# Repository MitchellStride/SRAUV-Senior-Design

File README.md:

# SRAUV-Senior-Design

## RPi Expansion PCB

## Cheap Quick Eth Breakout

## RGB Indicator Potted

## Misc. Small Breakouts & Leak Sensor

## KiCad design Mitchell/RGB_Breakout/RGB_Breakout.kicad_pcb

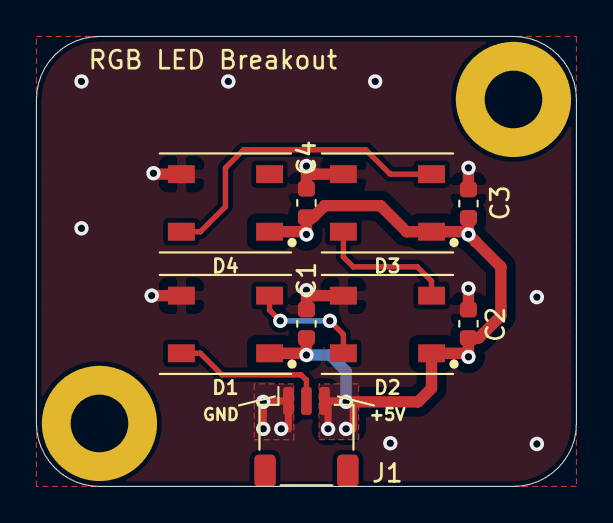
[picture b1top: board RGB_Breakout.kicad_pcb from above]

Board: 2 copper layers, 30.0 x 25.0 mm, 11 parts (0 on the bottom side), 6 nets.

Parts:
C1, C2, C3, C4: 1u; C_0603_1608Metric
D1, D2, D3, D4: WS2812B; LED_WS2812B_PLCC4_5.0x5.0mm_P3.2mm_SILKMOD
H1, H2: M3; MountingHole_3.2mm_M3_Pad
J1: RGB LED; JST_SH_SM03B-SRSS-TB_1x03-1MP_P1.00mm_Horizontal

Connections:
+5V: C1.1, C2.1, C3.1, C4.1, D1.1, D2.1, D3.1, D4.1, J1.3
/LED_DATA: D1.4, J1.2
GND: C1.2, C2.2, C3.2, C4.2, D1.3, D2.3, D3.3, D4.3, J1.1
unnamed: D1.2, D2.4
unnamed: D2.2, D3.4
unnamed: D3.2, D4.4

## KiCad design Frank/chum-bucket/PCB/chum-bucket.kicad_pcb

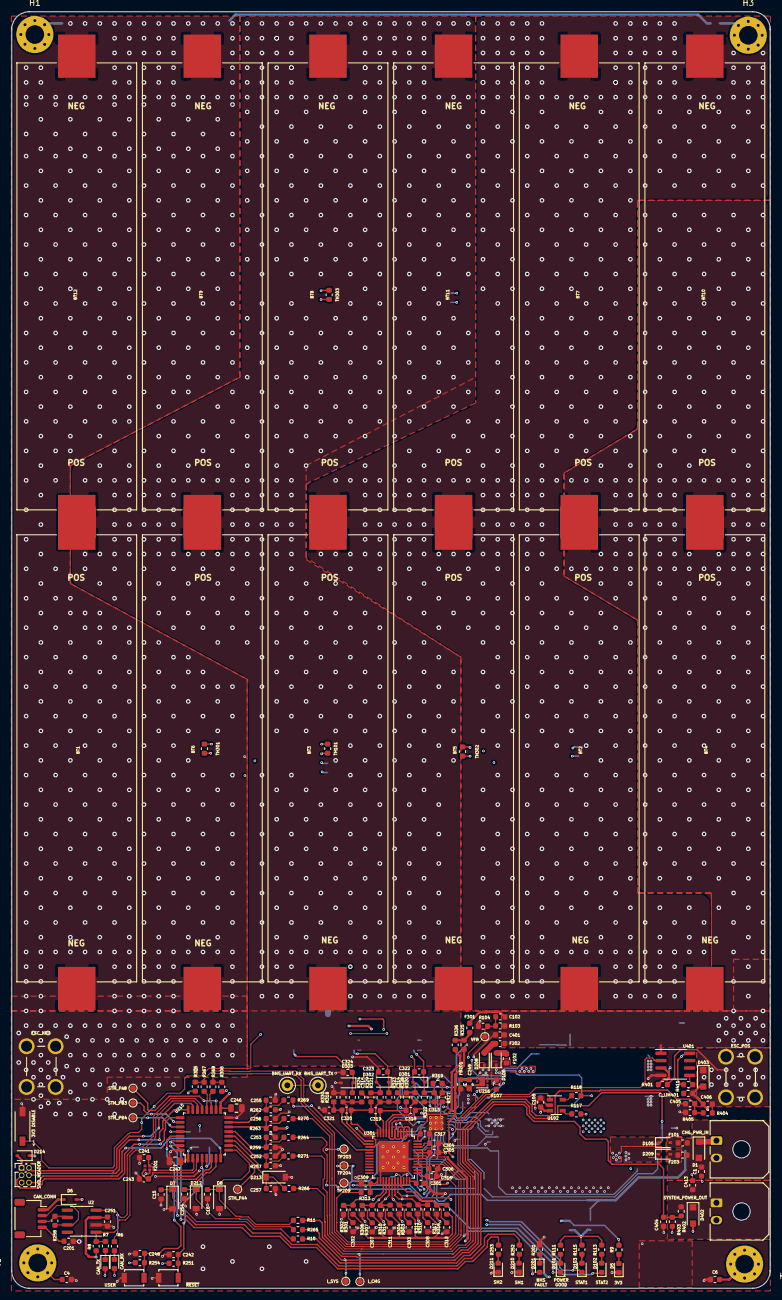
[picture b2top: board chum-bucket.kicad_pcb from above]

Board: 4 copper layers, 130.7 x 220.0 mm, 272 parts (0 on the bottom side), 135 nets.

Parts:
<- 3V3 DISABLE: LV_EN; CHS-01TB
BMS_UART_RX: STM_TX; TestPoint_Keystone_5000-5004_Miniature
BMS_UART_TX: STM_RX; TestPoint_Keystone_5000-5004_Miniature
BT1, BT2, BT3, BT4, BT5, BT6, BT7, BT8, BT9, BT10, BT11, BT12, BT13, BT14, BT15, BT16, BT17, BT18, BT19, BT20, BT21, BT22, BT23, BT24: 18650; Keystone_1042p_18650_Holder
C1, C3, C4, C5, C6, C118, C119, C201, C252, C253, C255, C256, C302, C303, C307, C308, C311, C312, C404, C405, C406, C413: 10nF; C_0603_1608Metric
C15, C16, C104, C108, C113, C114, C120, C242, C248, C251, C254, C257: 0.1uF; C_0603_1608Metric
C101, C103, C109, C245, C246, C247: 1uF; C_0805_2012Metric
C102: 22pF; C_0603_1608Metric
C105, C111, C115: 0.1u; C_0603_1608Metric
C106, C110, C112, C116, C117: 10uF; C_2220_5650Metric
C107: 22nF; C_0805_2012Metric
C224, C313, C314, C315, C401: 1uF; C_0603_1608Metric
C241, C243: 10p; C_0603_1608Metric
C249, C301, C304, C305, C306, C309: 2.2uF; C_0603_1608Metric
C310: 4.7uF; C_0805_2012Metric
C316, C317: 0.33uF; C_0603_1608Metric
C318, C319, C320, C321: 0.47uF; C_0603_1608Metric
C322, C323, C324: 1nF; C_0603_1608Metric
CAN_CONN: CAN_CONN; JST_SH_SM04B-SRSS-TB_1x04-1MP_P1.00mm_Horizontal
CAN_RX: GN; D_0603_1608Metric
CAN_TX: GN; D_0603_1608Metric
CHG_PWR_IN: UMBILLICAL_PWR; Molex_Micro-Fit_3.0_43650-0200_1x02_P3.00mm_Horizontal
C_LIM401: 10nF; C_0603_1608Metric
D1, D402: SMF24A; D_SOD-123F
D5, D101, D102, D103, D210, D211: GN; LED_0603_1608Metric
D6, D105, D106, D208, D209, D214: CUS520; D_SOD-323
D7, D8, D212, D213: BZT52; D_SOD-123
D104: BAT54T1G; D_SOD-123F
D201: RD; LED_0603_1608Metric
D301, D302, D303: BAS16; D_SOD-323
D403: SMF14A; D_SOD-123F
ESC_NEG: ESC_GND; Keystone_7771
ESC_POS: ESC_PWR; Keystone_7771
F101, F102: 100mA; Fuse_0603_1608Metric
F202, F203, F301: 200mA; Fuse_0603_1608Metric
FB201: BLM18; L_0603_1608Metric
H1: Top_Left; MountingHole_3.2mm_M3_Pad_Via
H2: Bot_Left; MountingHole_3.2mm_M3_Pad_Via
H3: Top_Right; MountingHole_3.2mm_M3_Pad_Via
H4: Bot_Right; MountingHole_3.2mm_M3_Pad_Via
I_CHG: TP_I_CHARGE; TestPoint_Pad_D1.0mm
I_SYS: TP_I_SYS; TestPoint_Pad_D1.0mm
L101: 6.8uH; icantdesignbuckconverters
Q101: 2N7002K; SOT-23
Q102, Q201: BSS84; SOT-23
Q103: SIS413DN
Q301, Q302, Q303: AON2406
Q401: SIR140DP
R1, R112, R114, R117, R118, R128, R264, R267, R268, R269, R270, R271, R313, R401, R411: 0; R_0603_1608Metric
R6, R7, R8, R101, R105, R108, R257, R259, R262, R263, R305, R306, R402, R404: 10k; R_0603_1608Metric
R9, R111, R113, R115, R126, R201, R251, R252, R253, R254, R322, R323, R324: 1k; R_0603_1608Metric
R10, R11, R121, R123, R265, R266, R318, R319, R320, R321, R326: 100; R_0603_1608Metric
R102: 3.3k; R_0603_1608Metric
R103: 499k; R_0603_1608Metric
R104, R127: 100k; R_0603_1608Metric
R106, R110: 330; R_0603_1608Metric
R107: 10; R_0603_1608Metric
R109: 15k; R_0603_1608Metric
R116, R122: 10m; R_1206_3216Metric
R119: 9.31k; R_0603_1608Metric
R120: 430k; R_0603_1608Metric
R124, R125: 68k; R_0603_1608Metric
R258: 120; R_0603_1608Metric
R301, R302, R303, R304, R307, R308, R310, R311, R314, R315, R316, R317: R; R_0603_1608Metric
R325: 40; R_0603_1608Metric
R327, R328, R329, R330: 47; R_0603_1608Metric
R331, R332, R333: 4; R_2512_6332Metric
R403: 1.5k; R_0603_1608Metric
R405: 3.6k; R_0603_1608Metric
RIN_1: 100; R_0603_1608Metric
STM_PA4, STM_PA8: TestPoint; TestPoint_Pad_D1.0mm
STM_PB3, STM_PB4: TestPoint; TestPoint_Pad_D1.0mm
SW: SW_NODE; TestPoint_Pad_D1.0mm
SWD_HEADER: SWD_DIAGS; PinHeader_2x03_P1.27mm_Vertical
SYSTEM_POWER_OUT: LV_PWR; Molex_Micro-Fit_3.0_43650-0200_1x02_P3.00mm_Horizontal
TH101, TH301, TH302, TH303, TH304, TH305, TH306: NTC_TERM; R_0603_1608Metric
TP203: BQ_Wake; TestPoint_Pad_D1.0mm
TP204: BQ_Fault; TestPoint_Pad_D1.0mm
TP209: TP_BQ2417_CHG_EN; TestPoint_Pad_D1.0mm
U2: SN65HVD232; SOIC-8_3.9x4.9mm_P1.27mm
U100: BTS6142DAUMA1; TO-252-4
U101: BQ2461x; VQFN-24-1EP_4x4mm_P0.5mm_EP2.45x2.45mm_ThermalVias
U102: INA196; SOT-23-5
U103: CSD87331; CSD87331Q3D
U215: STM32F042K6Tx; LQFP-32_7x7mm_P0.8mm
U216: TPS70933DRVT; WSON-6-1EP_2x2mm_P0.65mm_EP1x1.6mm
U301: BQ79606; LQFP-48-1EP_7x7mm_P0.5mm_EP4x4mm_Thermalvias
U401: MIC5014; SOIC-8_3.9x4.9mm_P1.27mm
USER: B3U-1000P; SW_SPST_B3U-1000P
VFB: VFB; TestPoint_Pad_D1.0mm
Y201: XTAL; ECX-1048

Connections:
+3V3: C108.2, C245.2, C246.2, C247.2, C251.1, C310.1, CAN_RX.2, CAN_TX.2, D6.2, D214.1, FB201.2, Q201.2, R8.1, R9.1, R112.1, R251.1, R254.1, R262.1, R263.1, R305.2, R306.2, U2.3, U102.3, U215.1, U215.5, U215.17, U301.33
+BATT: BT2.1, BT4.1, BT7.1, BT10.1, BT13.1, BT16.1, BT19.1, BT22.1, C102.1, C115.1, C116.1, C117.1, C401.1, F202.2, F301.1, Q103.2, Q401.3, R103.1, R118.2, R122.1, R319.1, R327.1, R331.2, U101.13, U401.1
/BATT_MGMT/BQ79606A_PWR_FUSED: F301.2, R325.1, R326.1
/BATT_MGMT/BQ79606_BAT: C317.1, R326.2, U301.48
/BATT_MGMT/BQ79606_LDOIN: C316.1, R325.2, U301.37
/BATT_MGMT/BQ79606_WAKE: R269.1, U301.16
/BATT_MGMT/CELL_BAL_0: C315.2, R318.2, R324.2, U301.13
/BATT_MGMT/CELL_BAL_1: C314.2, C315.1, R321.2, R323.2, U301.11
/BATT_MGMT/CELL_BAL_2: C313.2, C314.1, R320.2, R322.2, U301.9
/BATT_MGMT/CELL_BAL_3: C313.1, R319.2, U301.1, U301.3, U301.5, U301.7
/BATT_MGMT/CELL_FILT_0: C320.2, C321.1, R330.2, U301.14
/BATT_MGMT/CELL_FILT_1: C319.2, C320.1, R329.2, U301.12
/BATT_MGMT/CELL_FILT_2: C318.2, C319.1, R328.2, U301.10
/BATT_MGMT/CELL_FILT_3: C318.1, R327.2, U301.2, U301.4, U301.6, U301.8
/BATT_MGMT/SERIES_BANK_1: BT1.1, BT3.2, BT5.2, BT6.1, BT8.2, BT9.1, BT11.2, BT12.1, BT14.2, BT15.1, BT17.2, BT18.1, BT20.2, BT21.1, BT23.2, BT24.1, C323.2, D302.2, Q302.3, R321.1, R329.1, R333.2
/BATT_MGMT/SERIES_BANK_2: BT2.2, BT3.1, BT4.2, BT5.1, BT7.2, BT8.1, BT10.2, BT11.1, BT13.2, BT14.1, BT16.2, BT17.1, BT19.2, BT20.1, BT22.2, BT23.1, C322.2, D301.2, Q301.3, R320.1, R328.1, R332.2
/BATT_MGMT/THERM1: C302.1, R301.2, R302.1, TH301.2, U301.27
/BATT_MGMT/THERM2: C307.1, R307.2, R308.1, TH303.2, U301.28
/BATT_MGMT/THERM3: C311.1, R314.2, R315.1, TH305.2, U301.29
/BATT_MGMT/THERM4: C303.1, R303.2, R304.1, TH302.2, U301.30
/BATT_MGMT/THERM5: C308.1, R310.2, R311.1, TH304.2, U301.31
/BATT_MGMT/THERM6: C312.1, R316.2, R317.1, TH306.2, U301.32
/BATT_MGMT/TSREF: R301.1, R303.1, R307.1, R310.1, R314.1, R316.1, TH301.1, TH302.1, TH303.1, TH304.1, TH305.1, TH306.1, U301.43
/BATT_MGMT/UART_BQ79606_STM_JMP_N: BMS_UART_RX.1, R268.1, R306.1, U301.41
/BATT_MGMT/UART_BQ79606_STM_JMP_P: BMS_UART_TX.1, R267.1, R305.1, U301.40
/BATT_MGMT/~BQ79606_FAULT: Q201.1, R270.1, TP203.1, U301.42
/CHARGER/ACSET: R108.2, R109.1, U101.16
/CHARGER/ANALOG_I_CHG: I_CHG.1, R266.1, U102.1
/CHARGER/ANALOG_I_SYS: I_SYS.1, R110.1, R265.1, U100.4
/CHARGER/BQ24617_CHG_EN: R264.1, TP209.1, U101.4
/CHARGER/BQ24617_PG: D101.1, R1.1, TP204.1, U101.8
/CHARGER/BQ_24617_VFB: C102.2, R103.2, R104.1, U101.12, VFB.1
/CHARGER/CHG_THERM: C113.2, R121.2, U101.6
/CHARGER/ISET1: R101.2, R102.1, U101.11
/CHARGER/ISET2: R105.2, R106.1, U101.15
/CHARGER/I_CHG_JMP_N: R118.1, U102.5
/CHARGER/I_CHG_JMP_P: R117.1, U102.4
/CHARGER/I_CHG_P: C114.2, C115.2, L101.2, R117.2, R122.2, U101.14
/CHARGER/I_SYS_P: C104.2, C105.2, R116.2, U100.1, U100.5, U101.2
/CHARGER/STAT1: D103.1, U101.5
/CHARGER/STAT2: D102.1, U101.9
/CHARGER/SYS_PWR_OUT: C105.1, C106.1, C110.1, C112.1, C120.1, C413.2, D402.1, F102.2, Q103.3, R116.1, R127.2, R402.1, SYSTEM_POWER_OUT.1, U101.1, U103.1
/CHARGER/VREF: C101.2, R101.1, R105.1, R108.1, R119.1, U101.10
/CHARGER/~AC_DRV: R128.1, U101.3
/CHARGER/~BATTDRV: R126.2, U101.23
/CHARGER/~CHG_LS_EN: RIN_1.1, U100.2
/MCU/ANALOG_I_CHG_JMP: C257.1, D213.1, R266.2, U215.11
/MCU/ANALOG_I_SYS_JMP: C254.1, D212.1, R265.2, U215.7
/MCU/ANALOG_V_ESCS: C405.2, R11.1, R404.2, R405.1
/MCU/ANALOG_V_ESCS_JMP: C16.1, D8.1, R11.2, U215.9
/MCU/ANALOG_V_SYSTEM: C404.2, R10.1, R402.2, R403.1
/MCU/ANALOG_V_SYSTEM_JMP: C15.1, D7.1, R10.2, U215.6
/MCU/BQ24617_PG_JMP: R1.2, U215.28
/MCU/BQ79606_WAKE_JMP: C255.2, R262.2, R269.2, U215.15
/MCU/BQ_24617_CHG_EN_JMP: C253.1, R259.1, R264.2, U215.13
/MCU/CHG_PWR_UNFUSED: C1.1, CHG_PWR_IN.2, D1.2, F101.2, F203.2, Q102.2, R114.1, R125.1, U100.3
/MCU/ESC_PWR_EN: R271.1, U401.2
/MCU/ESC_PWR_EN_JMP: C252.1, R257.1, R271.2, U215.12
/MCU/SM0_LED: R252.1, U215.31
/MCU/SM1_LED: R253.1, U215.30
/MCU/STM32_SWCLK: SWD_HEADER.4, U215.24
/MCU/STM32_SWDIO: SWD_HEADER.2, U215.23
/MCU/STM_PA4: STM_PA4.1, U215.10
/MCU/STM_PA8: STM_PA8.1, U215.18
/MCU/STM_PB3: STM_PB3.1, U215.26
/MCU/STM_PB4: STM_PB4.1, U215.27
/MCU/UART_BQ79606_STM_N: R268.2, U215.19
/MCU/UART_BQ79606_STM_P: R267.2, U215.20
/MCU/UART_CAN_STM_N: R7.2, R8.2, U2.1, U215.22
/MCU/UART_CAN_STM_P: R6.2, U2.4, U215.21
/MCU/UART_DIAGS_STM_RX: SWD_HEADER.3, U215.25
/MCU/UART_DIAGS_STM_TX: SWD_HEADER.6, U215.8
/MCU/USR_BUTTON: C248.2, R254.2, U215.29, USER.2
/MCU/XTAL_N: C243.1, U215.3, Y201.3
/MCU/XTAL_P: C241.1, U215.2, Y201.1
/MCU/~BQ79606_FAULT_JMP: C256.2, R263.2, R270.2, U215.14
/MCU/~RESET: C242.2, R251.2, U215.4
/SYS_MGMT/ESC_PWR_OUT: C406.2, D403.1, ESC_POS.1, Q401.1, R401.2, R404.1
GND: <- 3V3 DISABLE.2, BT1.2, BT6.2, BT9.2, BT12.2, BT15.2, BT18.2, BT21.2, BT24.2, C1.2, C3.2, C4.2, C5.2, C6.2, C15.2, C16.2, C101.1, C103.1, C104.1, C106.2, C107.2, C108.1, C109.1, C110.2, C112.2, C113.1, C114.1, C116.2, C117.2, C118.1, C119.1, C201.2, C224.1, C241.2, C242.1, C243.2, C245.1, C246.1, C247.1, C248.1, C249.1, C251.2, C252.2, C253.2, C254.2, C255.1, C256.1, C257.2, C301.2, C302.2, C303.2, C304.2, C305.2, C306.2, C307.2, C308.2, C309.2, C310.2, C311.2, C312.2, C316.2, C317.2, C321.2, C324.2, C401.2, C404.1, C405.1, C406.1, C413.1, CHG_PWR_IN.1, C_LIM401.2, D1.1, D5.1, D7.2, D8.2, D210.1, D211.1, D212.2, D213.2, D303.2, D402.2, D403.2, ESC_NEG.1, Q101.2, Q303.3, R102.2, R104.2, R106.2, R109.2, R110.2, R120.2, R124.2, R201.2, R257.2, R259.2, R302.2, R304.2, R308.2, R311.2, R315.2, R317.2, R318.1, R330.1, R403.2, R405.2, SWD_HEADER.5, SYSTEM_POWER_OUT.2, TH101.2, U2.2, U101.17, U101.25, U102.2, U103.8, U215.16, U215.32, U216.3, U216.7, U301.15, U301.26, U301.35, U301.45, U301.49, U401.4, USER.1, Y201.4
unnamed: C3.1, H1.1
unnamed: C4.1, H2.1
unnamed: C5.1, H3.1
unnamed: C6.1, H4.1
unnamed: C103.2, R107.1, U101.24
unnamed: C107.1, U101.7
unnamed: C109.2, D104.2, U101.18
unnamed: C111.1, D104.1, U101.22
unnamed: C111.2, U101.20, U103.3
unnamed: C118.2, Q102.3, R123.1, R124.1
unnamed: C119.2, Q102.1, R125.2, R128.2
unnamed: C120.2, Q103.1, R126.1, R127.1
unnamed: C201.1, CAN_CONN.4
unnamed: C224.2, D208.1, D209.1, U216.6
unnamed: C249.2, FB201.1, U216.1
unnamed: C301.1, U301.36
unnamed: C304.1, U301.46
unnamed: C305.1, U301.44
unnamed: C306.1, R313.2, U301.39
unnamed: C309.1, R313.1, U301.25
unnamed: C322.1, D301.1, Q301.2, R322.1
unnamed: C323.1, D302.1, Q302.2, R323.1
unnamed: C324.1, D303.1, Q303.2, R324.1
unnamed: C_LIM401.1, R411.1, U401.5
unnamed: CAN_RX.1, R6.1
unnamed: CAN_TX.1, R7.1
unnamed: D5.2, R9.2
unnamed: CAN_CONN.1, D6.1
unnamed: D101.2, R111.2
unnamed: D102.2, R113.2
unnamed: D103.2, R115.2
unnamed: D105.1, D106.1, R107.2
unnamed: D105.2, F101.1
unnamed: D106.2, F102.1
unnamed: D201.1, R201.1
unnamed: D201.2, Q201.3
unnamed: D208.2, F202.1
unnamed: D209.2, F203.1
unnamed: D210.2, R252.2
unnamed: D211.2, R253.2
unnamed: D214.2, SWD_HEADER.1
unnamed: CAN_CONN.2, R258.1, U2.7
unnamed: CAN_CONN.3, R258.2, U2.6
unnamed: L101.1, SW.1, U103.5
unnamed: Q101.1, R123.2
unnamed: Q101.3, RIN_1.2
unnamed: Q301.1, R331.1
unnamed: Q302.1, R332.1
unnamed: Q303.1, R333.1
unnamed: Q401.2, R411.2
unnamed: R111.1, R112.2, R113.1, R114.2, R115.1
unnamed: R119.2, R120.1, R121.1, TH101.1
unnamed: R401.1, U401.3
unnamed: <- 3V3 DISABLE.1, U216.4
unnamed: U101.19, U103.4
unnamed: U101.21, U103.2

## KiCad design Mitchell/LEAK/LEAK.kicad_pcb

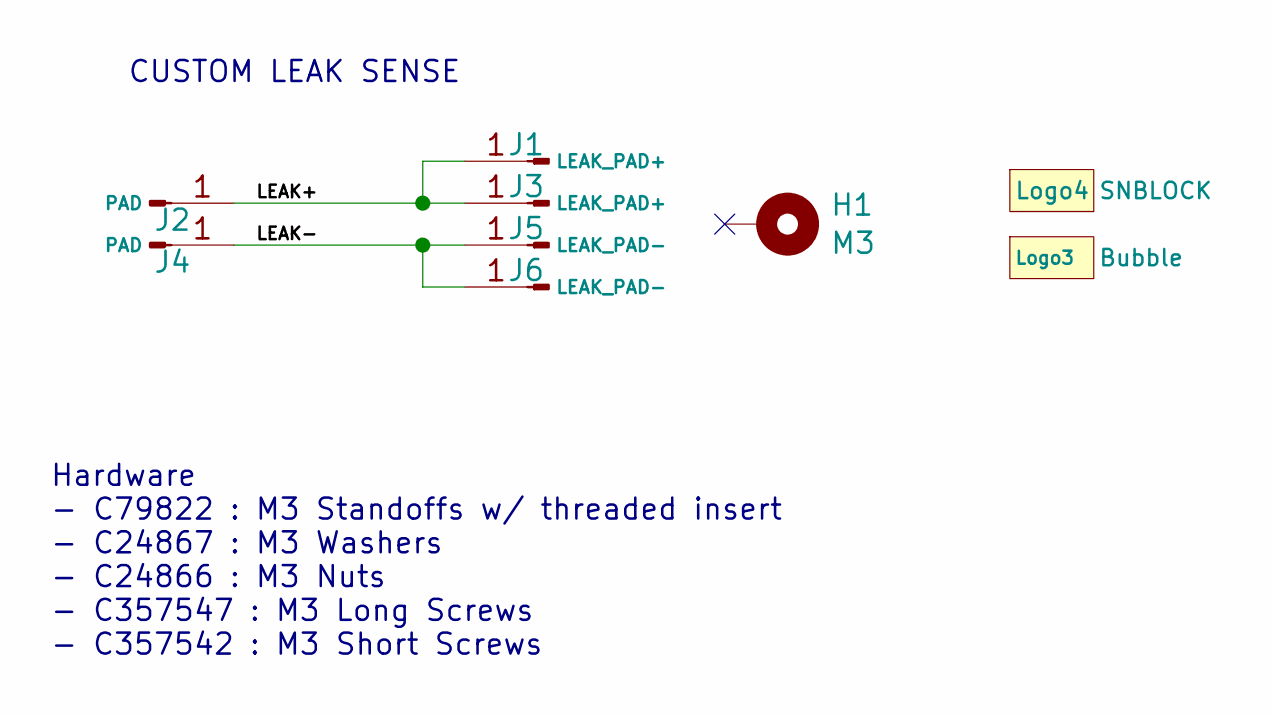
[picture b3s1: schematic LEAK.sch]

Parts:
H1: M3; MountingHole_3.2mm_M3_Pad
J1, J3: LEAK_PAD+; LEAK_PAD
J2, J4: PAD; LEAK_PAD
J5, J6: LEAK_PAD-; LEAK_PAD
Logo3: Bubble; bubbles
Logo4: SNBLOCK; SN_BLOCK

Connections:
/LEAK+: J1.1, J2.1, J3.1
/LEAK-: J4.1, J5.1, J6.1

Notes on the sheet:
CUSTOM LEAK SENSE
Hardware - C79822 : M3 Standoffs w/ threaded insert - C24867 : M3 Washers - C24866 : M3 Nuts - C357547 : M3 Long Screws - C357542 : M3 Short Screws

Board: 2 copper layers, 9 parts (1 on the bottom side), 2 nets, no tracks yet.

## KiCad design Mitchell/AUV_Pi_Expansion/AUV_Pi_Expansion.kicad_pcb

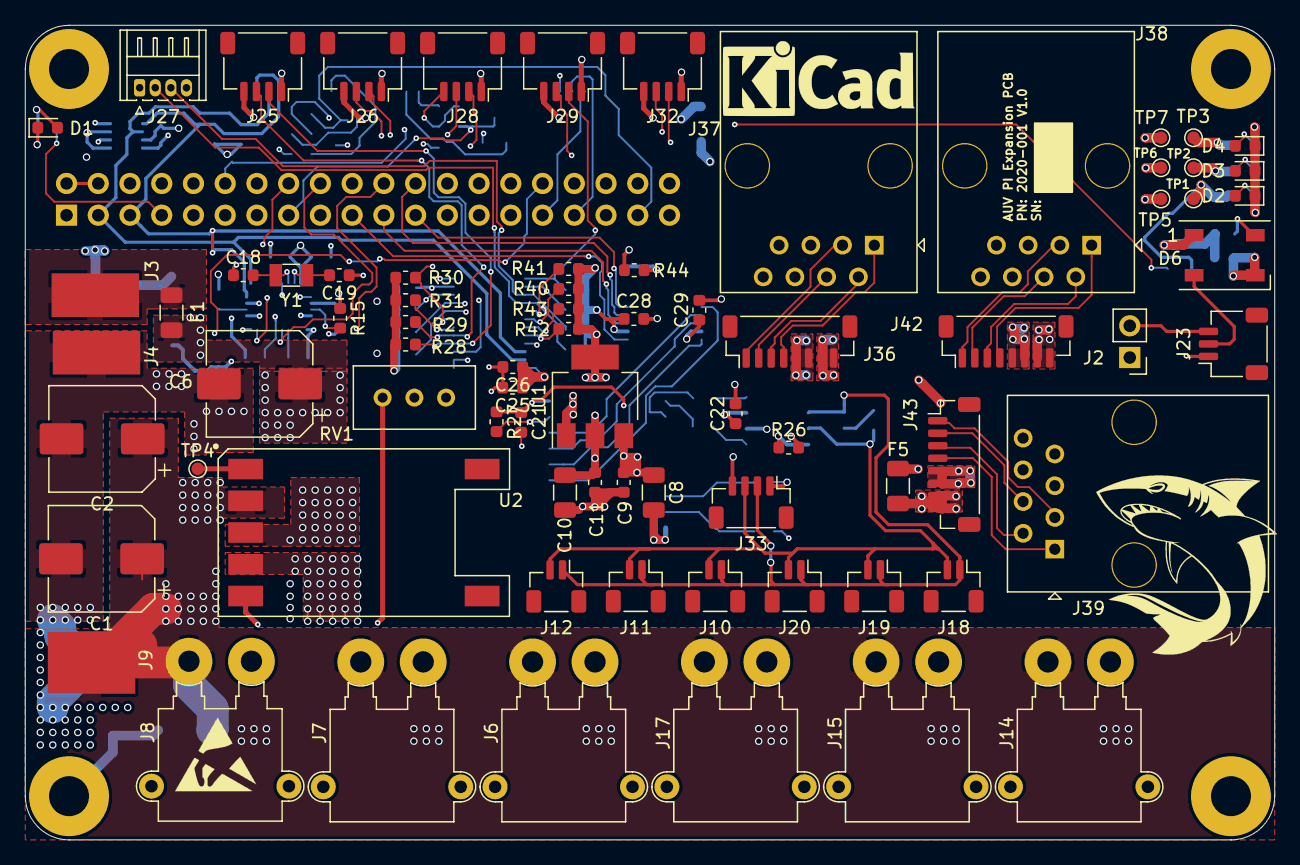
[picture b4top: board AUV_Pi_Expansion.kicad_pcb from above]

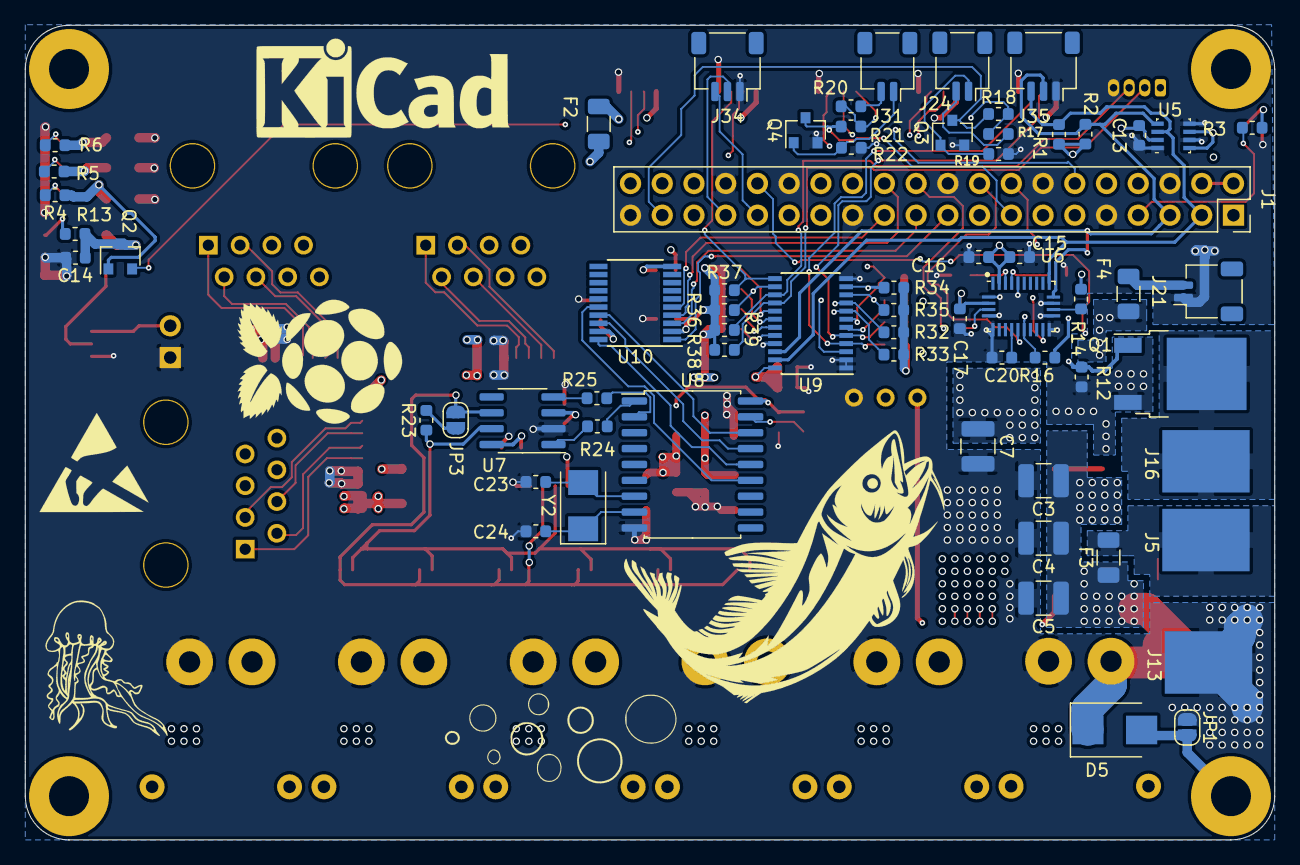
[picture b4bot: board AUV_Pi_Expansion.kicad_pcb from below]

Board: 4 copper layers, 100.0 x 65.2 mm, 154 parts (71 on the bottom side), 90 nets.

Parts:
C1, C2, C6: 100u; CP_Elec_8x10
C3, C4, C5, C7: 4.7u; C_1210_3225Metric
C8, C10: 10u; C_1206_3216Metric
C9, C11, C14, C25: 1u; C_0603_1608Metric
C13, C17, C20, C21, C22, C26, C28, C29: 0.1u; C_0603_1608Metric
C15: 6.8n; C_0603_1608Metric
C16: 120n; C_0603_1608Metric
C18, C19, C23, C24: 22p; C_0603_1608Metric
D1, D2: 3V3; LED_0603_1608Metric
D3: 5V; LED_0603_1608Metric
D4: +V; LED_0603_1608Metric
D5: 26.7 Vb; D_SMB
D6: WS2812B; LED_WS2812B_PLCC4_5.0x5.0mm_P3.2mm
F1, F3, F5: 5A; Fuse_1206_3216Metric
F2, F4: 1A; Fuse_1206_3216Metric
H1, H2, H3, H4: M3; MountingHole_3.2mm_M3_Pad
J1: 40HAT; PinSocket_2x20_P2.54mm_Vertical
J2: FAN; PinHeader_1x02_P2.54mm_Vertical
J3: PWR+; WtB_Solder_Pad_7x3.5
J4: PWR-; WtB_Solder_Pad_7x3.5
J5, J9: PWR+; WtB_Solder_Pad_0.7x0.5
J6: ESC3P; XT30PW-M
J7: ESC2P; XT30PW-M
J8: ESC1P; XT30PW-M
J10: ESC3C; JST_SH_BM02B-SRSS-TB_1x02-1MP_P1.00mm_Vertical
J11: ESC2C; JST_SH_BM02B-SRSS-TB_1x02-1MP_P1.00mm_Vertical
J12: ESC1C; JST_SH_BM02B-SRSS-TB_1x02-1MP_P1.00mm_Vertical
J13, J16: PWR-; WtB_Solder_Pad_0.7x0.5
J14: ESC6P; XT30PW-M
J15: ESC5P; XT30PW-M
J17: ESC4P; XT30PW-M
J18: ESC6C; JST_SH_BM02B-SRSS-TB_1x02-1MP_P1.00mm_Vertical
J19: ESC5C; JST_SH_BM02B-SRSS-TB_1x02-1MP_P1.00mm_Vertical
J20: ESC4C; JST_SH_BM02B-SRSS-TB_1x02-1MP_P1.00mm_Vertical
J21: N_SWITCH; JST_SH_SM02B-SRSS-TB_1x02-1MP_P1.00mm_Horizontal
J23: RGB LED; JST_SH_SM03B-SRSS-TB_1x03-1MP_P1.00mm_Horizontal
J24: LEAK1; JST_SH_SM02B-SRSS-TB_1x02-1MP_P1.00mm_Horizontal
J25: TOF1; JST_SH_SM04B-SRSS-TB_1x04-1MP_P1.00mm_Horizontal
J26: TOF2; JST_SH_SM04B-SRSS-TB_1x04-1MP_P1.00mm_Horizontal
J27: BlueRobotics Pressure Sense; Hirose_DF13-04P-1.25DS_1x04_P1.25mm_Horizontal
J28: TOF3; JST_SH_SM04B-SRSS-TB_1x04-1MP_P1.00mm_Horizontal
J29: TOF4; JST_SH_SM04B-SRSS-TB_1x04-1MP_P1.00mm_Horizontal
J31: LEAK2; JST_SH_SM02B-SRSS-TB_1x02-1MP_P1.00mm_Horizontal
J32: TOF5; JST_SH_SM04B-SRSS-TB_1x04-1MP_P1.00mm_Horizontal
J33: CAN; JST_SH_BM04B-SRSS-TB_1x04-1MP_P1.00mm_Vertical
J34: GPIO; JST_SH_SM03B-SRSS-TB_1x03-1MP_P1.00mm_Horizontal
J35: I2C; JST_SH_SM03B-SRSS-TB_1x03-1MP_P1.00mm_Horizontal
J36: Rpi Z 1 - IN; JST_SH_BM08B-SRSS-TB_1x08-1MP_P1.00mm_Vertical
J37: Rpi Z 1 - OUT SWITCH; DS1128-05-S8B8P
J38: Rpi Z 2 - OUT SWITCH; DS1128-05-S8B8P
J39: Rpi Z 3 - OUT SWITCH; DS1128-05-S8B8P
J42: Rpi Z 2 - IN; JST_SH_BM08B-SRSS-TB_1x08-1MP_P1.00mm_Vertical
J43: Rpi Z 3 - IN; JST_SH_BM08B-SRSS-TB_1x08-1MP_P1.00mm_Vertical
JP1: CGND; SolderJumper-2_P1.3mm_Open_RoundedPad1.0x1.5mm
JP3: C120; SolderJumper-2_P1.3mm_Open_RoundedPad1.0x1.5mm
Logo1: SNBLOCK; SN_BLOCK
Logo6: ESD1; ESD-Logo_6.6x6mm_SilkScreen
Logo7: ESD2; ESD-Logo_8.9x8mm_SilkScreen
Logo8: KiCad; KiCad-Logo_6mm_SilkScreen
Logo9: KiCad2; KiCad-Logo_8mm_SilkScreen
Logo10: RPI; rasp_pi
Logo11: Shark; shark_clip
Logo14: Jelly; jelly
Logo16: Bubble; bubbles
Logo18: Cod; cod
Q1: Q_NMOS_GDS; TO-252-2
Q2, Q3, Q4: MMBT3904; SOT-23
R1, R2, R28, R29, R30, R31, R32, R33, R34, R35, R36, R37, R38, R39, R40, R41, R42, R43: 3.9k; R_0603_1608Metric
R3, R4: 100; R_0603_1608Metric
R5, R17, R18, R20, R21, R26: 1k; R_0603_1608Metric
R6: 4.7k; R_0603_1608Metric
R12, R19, R22: 100k; R_0603_1608Metric
R13: 470; R_0603_1608Metric
R14, R15, R16, R27, R44: 10k; R_0603_1608Metric
R23: 120; R_0603_1608Metric
R24, R25: 0; R_0603_1608Metric
RV1: R_POT; Potentiometer_Bourns_3296W_Vertical
TP1: 3V3; TestPoint_Pad_D1.0mm
TP2: 5V; TestPoint_Pad_D1.0mm
TP3: +V; TestPoint_Pad_D1.0mm
TP4: SYS_ON/OFF; TestPoint_Pad_D1.0mm
TP5, TP6, TP7: GND; TestPoint_Pad_D1.0mm
U1: AZ1117-3.3; SOT-223-3_TabPin2
U2: SRBH-06H1A1G
U5: BME280; BME280_Mod_Bosch_LGA-8_2.5x2.5mm_P0.65mm_ClockwisePinNumber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
U6: BNO055; BNO055_MOD_LGA-28_5.2x3.8mm_P0.5mm
U7: SN65HVD230; SOIC-8_3.9x4.9mm_P1.27mm
U8: MCP2515-xSO; SOIC-18W_7.5x11.6mm_P1.27mm
U9: TCA9548APWR; TSSOP-24_4.4x7.8mm_P0.65mm
U10: TXS0108EPW; TSSOP-20_4.4x6.5mm_P0.65mm
Y1: 32.768kHz; Crystal_SMD_3215-2Pin_3.2x1.5mm
Y2: 8MHz; Crystal_SMD_5032-2Pin_5.0x3.2mm

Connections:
3V3_Sensors: F2.2, J25.4, J26.4, J27.1, J28.4, J29.4, J32.4, R17.2, R18.1, R20.2, R21.1
5V_EXT\POE: F5.2, J2.2, J23.3, J36.7, J36.8, J42.7, J42.8, J43.7, J43.8
5V_PI: F1.2, J3.1
5V_Router: F4.2, J21.2
+3V3: C10.1, C11.1, C13.1, C15.1, C16.1, C17.1, C25.1, C26.1, C28.1, F2.1, Q2.1, R1.1, R2.1, R4.1, R14.1, R15.1, R16.1, R28.1, R29.1, R30.1, R31.1, R32.1, R33.1, R34.1, R35.1, R36.1, R37.1, R38.1, R39.1, R40.1, R41.1, R42.1, R43.1, R44.1, TP1.1, U1.2, U5.2, U5.6, U5.8, U6.3, U6.28, U9.24, U10.2
+5V: C6.1, C7.1, C8.1, C9.1, C14.1, C21.1, C22.1, C29.1, D6.1, F1.1, F4.1, F5.1, J33.4, Q2.3, R5.1, R13.2, R27.1, TP2.1, U1.3, U2.4, U7.3, U8.18, U10.19
+V: C1.1, C2.1, C3.1, C4.1, C5.1, D5.1, F3.1, J6.2, J7.2, J8.2, J9.1, J14.2, J15.2, J17.2, R6.1, TP3.1, U2.2
/Interface/CAN_RX: R25.1, U8.2
/Interface/CAN_TX: R24.1, U8.1
/Interface/MCP_~RST: R27.2, U8.17
/Interface/TCA_SCL6: R40.2, U9.18
/Interface/TCA_SCL7: R42.2, U9.20
/Interface/TCA_SDA6: R41.2, U9.17
/Interface/TCA_SDA7: R43.2, U9.19
/LED_USR1: J1.7, R3.1
/P5V_HAT: J1.2, J1.4
/POE/Pi1_Data_TP_1-1: J36.4, J37.1
/POE/Pi1_Data_TP_1-2: J36.3, J37.2
/POE/Pi1_Data_TP_2-1: J36.1, J37.3
/POE/Pi1_Data_TP_2-2: J36.2, J37.4
/POE/Pi2_Data_TP_1-1: J38.1, J42.4
/POE/Pi2_Data_TP_1-2: J38.2, J42.3
/POE/Pi2_Data_TP_2-1: J38.3, J42.1
/POE/Pi2_Data_TP_2-2: J38.4, J42.2
/POE/Pi3_Data_TP_1-1: J39.1, J43.4
/POE/Pi3_Data_TP_1-2: J39.2, J43.3
/POE/Pi3_Data_TP_2-1: J39.3, J43.1
/POE/Pi3_Data_TP_2-2: J39.4, J43.2
/Power/SYS_ON\OFF: TP4.1, U2.1
/Sensors/BNO_ADDR_SEL: R14.2, U6.17
/Sensors/LEAK+_1: J24.2, R17.1
/Sensors/LEAK+_2: J31.2, R20.1
/Sensors/LEAK-_1: J24.1, Q3.1, R19.2
/Sensors/LEAK-_2: J31.1, Q4.1, R22.2
/Sensors/LED_CTRL: J16.1, Q1.2
/Sensors/LED_DATA: D6.2, J23.2
BNO_BL_IND: J1.18, U6.10
BNO_INT: J1.16, U6.14
BNO_~RST: J1.22, R16.2, U6.11
CANH: J10.2, J11.2, J12.2, J18.2, J19.2, J20.2, J33.3, R23.1, U7.7
CANL: J10.1, J11.1, J12.1, J18.1, J19.1, J20.1, J33.2, JP3.2, U7.6
CHASSIS: D5.2, H1.1, JP1.2
GCLK1\GPIO5: J1.29, U9.3
GCLK2\GPIO6: J1.31, J34.3
GND: C1.2, C2.2, C3.2, C4.2, C5.2, C6.2, C7.2, C8.2, C9.2, C10.2, C11.2, C13.2, C14.2, C15.2, C16.2, C17.2, C18.1, C19.1, C20.2, C21.2, C22.2, C23.1, C24.1, C25.2, C26.2, C28.2, C29.2, D1.1, D2.1, D3.1, D4.1, D6.3, J1.6, J1.9, J1.14, J1.20, J1.25, J1.30, J1.34, J1.39, J2.1, J4.1, J6.1, J7.1, J8.1, J13.1, J14.1, J15.1, J17.1, J21.1, J23.1, J25.1, J26.1, J27.4, J28.1, J29.1, J32.1, J33.1, J34.1, J35.1, J36.5, J36.6, J42.5, J42.6, J43.5, J43.6, JP1.1, Q1.3, Q3.2, Q4.2, R12.1, R19.1, R22.1, R26.2, RV1.3, TP5.1, TP6.1, TP7.1, U1.1, U2.3, U5.1, U5.5, U5.7, U6.2, U6.5, U6.6, U6.15, U6.16, U6.18, U6.25, U7.2, U8.9, U9.1, U9.2, U9.12, U9.21
G_DRV_LED: J1.32, Q1.1, R12.2
LEAK_1: J1.37, Q3.3, R18.2
LEAK_2: J1.15, Q4.3, R21.2
LED_PWR: F3.2, J5.1
LED_USR2: J1.12, Q2.2
MISO0\GPIO9: J1.21, U10.3
MOSI0\GPIO10: J1.19, U10.1
unnamed: C18.2, U6.26, Y1.1
unnamed: C19.2, U6.27, Y1.2
unnamed: C20.1, U6.9
unnamed: C23.2, U8.7, Y2.2
unnamed: C24.2, U8.8, Y2.1
unnamed: D1.2, R3.2
unnamed: D2.2, R4.2
unnamed: D3.2, R5.2
unnamed: D4.2, R6.2
unnamed: D6.4, R13.1
unnamed: JP3.1, R23.2
unnamed: R15.2, U6.4
unnamed: R24.2, U7.1
unnamed: R25.2, U7.4
unnamed: R26.1, U7.8
unnamed: R44.2, U10.10
unnamed: RV1.1, RV1.2, U2.5
unnamed: U8.13, U10.16
unnamed: U8.16, U10.17
unnamed: U8.15, U10.18
unnamed: U8.14, U10.20
PWM1\GPIO12: J1.33, J34.2
SCLK0\GPIO11: J1.23, U10.5
SCL\GPIO3: J1.5, J35.2, R2.2, U5.4, U6.19, U9.22
SDA\GPIO2: J1.3, J35.3, R1.2, U5.3, U6.20, U9.23
TCA_SCL0: J25.3, R28.2, U9.5
TCA_SCL1: J28.3, R30.2, U9.7
TCA_SCL2: J32.3, R32.2, U9.9
TCA_SCL3: J26.3, R34.2, U9.11
TCA_SCL4: J29.3, R36.2, U9.14
TCA_SCL5: J27.2, R38.2, U9.16
TCA_SDA0: J25.2, R29.2, U9.4
TCA_SDA1: J28.2, R31.2, U9.6
TCA_SDA2: J32.2, R33.2, U9.8
TCA_SDA3: J26.2, R35.2, U9.10
TCA_SDA4: J29.2, R37.2, U9.13
TCA_SDA5: J27.3, R39.2, U9.15
~CE0~\GPIO8: J1.24, U10.4

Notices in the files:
parts and their libraries:
Copyright 2016 Accelerated Designs. All rights reserved.
